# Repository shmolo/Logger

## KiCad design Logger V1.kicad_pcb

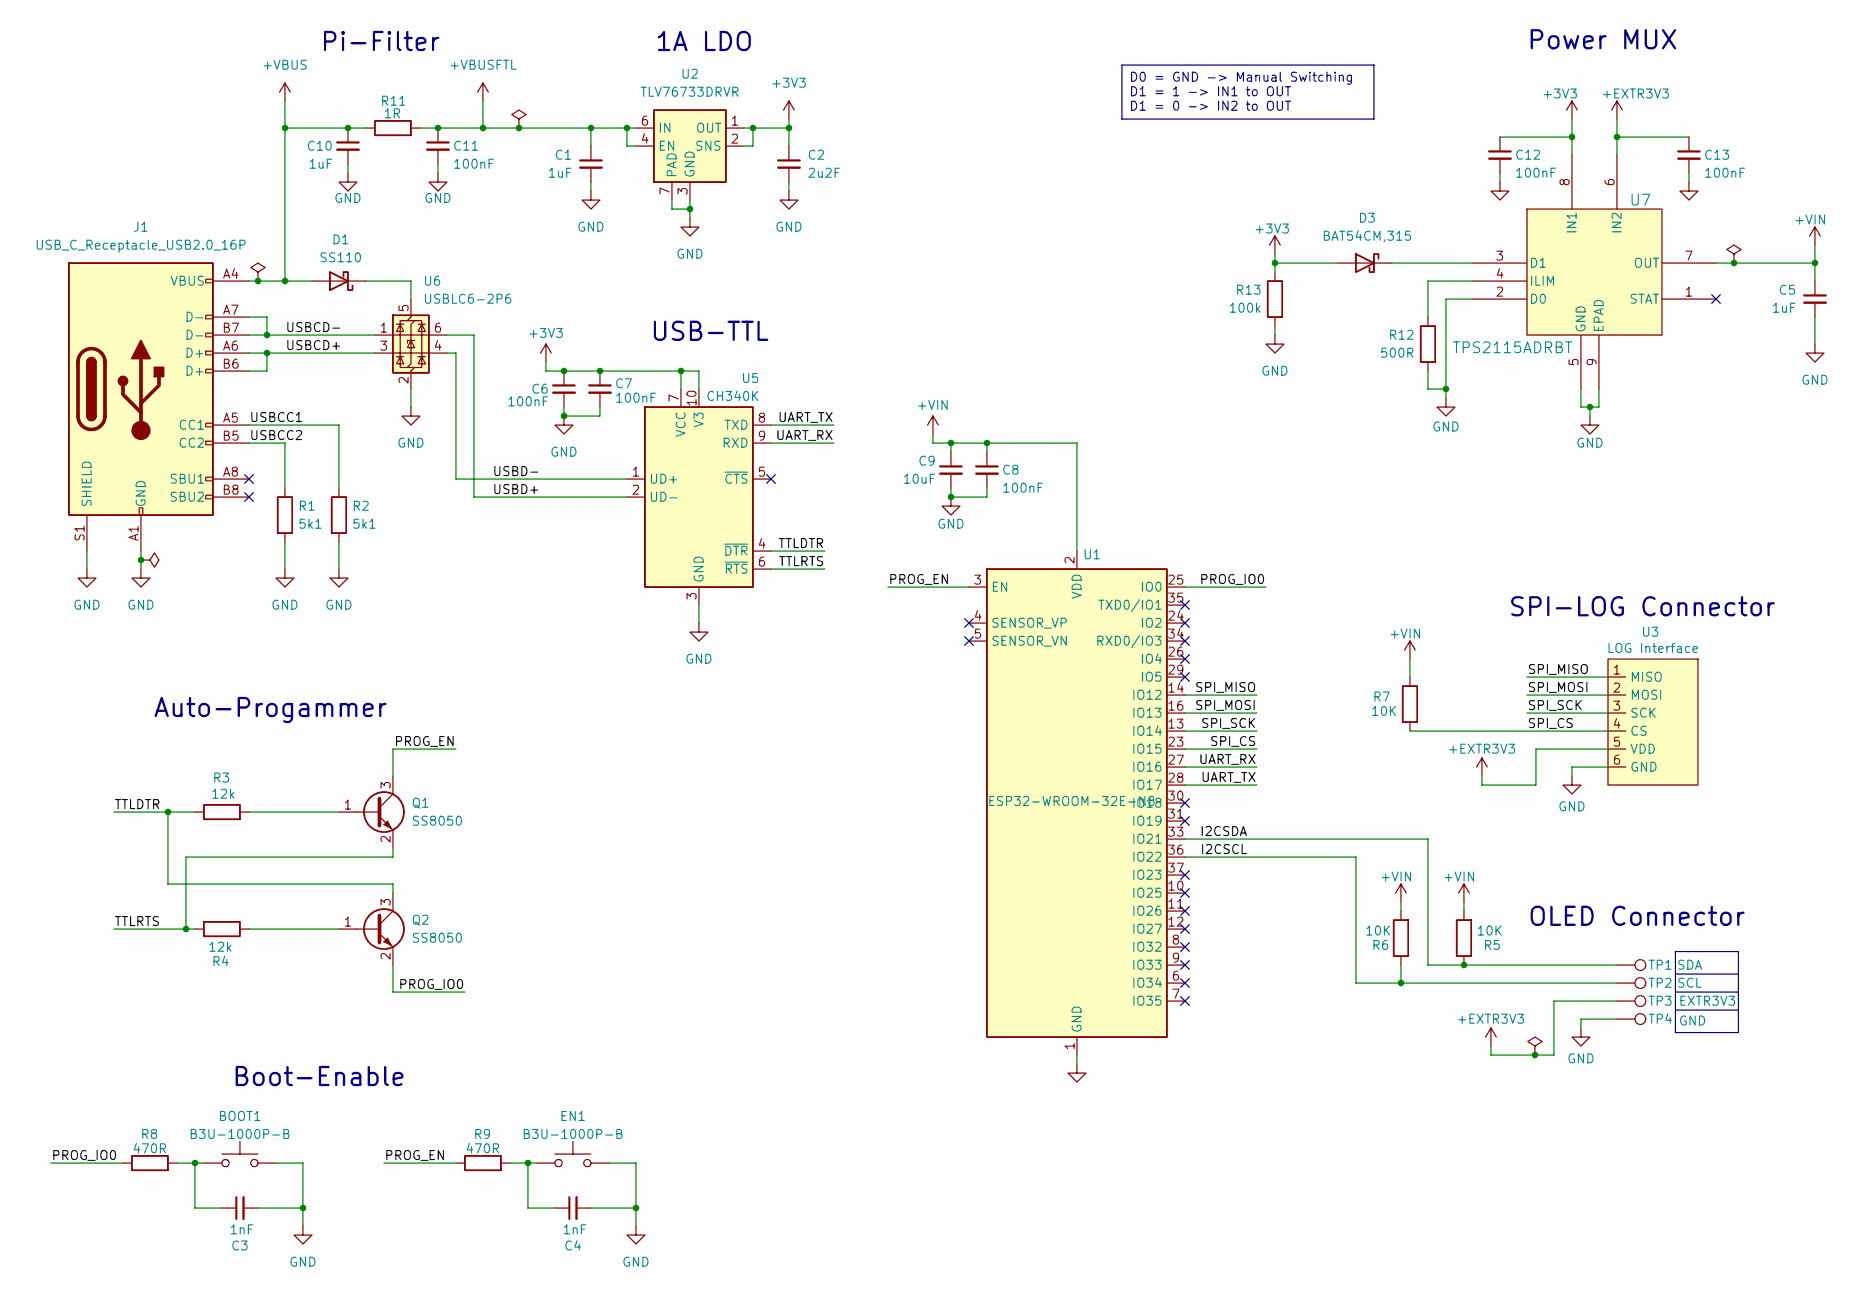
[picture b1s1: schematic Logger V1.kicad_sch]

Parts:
BOOT1: B3U-1000P-B; SW_SPST_B3U-1000P-B; JLC.NUM C231329
C1, C5, C10: 1uF; C_0603_1608Metric_Pad1.08x0.95mm_HandSolder; JLC.NUM C5673
C2: 2u2F; C_0603_1608Metric_Pad1.08x0.95mm_HandSolder; JLC.NUM C23630
C3, C4: 1nF; C_0402_1005Metric_Pad0.74x0.62mm_HandSolder; JLC.NUM C2649506
C6, C7, C8, C11, C12, C13: 100nF; C_0402_1005Metric_Pad0.74x0.62mm_HandSolder; JLC.NUM C100072
C9: 10uF; C_0603_1608Metric_Pad1.08x0.95mm_HandSolder; JLC.NUM C96446
D1: SS110; D_SMA; JLC.NUM C143192
D3: BAT54CM,315; Diodes_DFN1006-3; JLC.NUM C549275
EN1: B3U-1000P-B; SW_SPST_B3U-1000P-B; JLC.NUM C231329
J1: USB_C_Receptacle_USB2.0_16P; USB_C_Receptacle_GCT_USB4105-xx-A_16P_TopMnt_Horizontal; JLC.NUM C3020560
Q1, Q2: SS8050; SOT-23; JLC.NUM C111765
R1, R2: 5k1; R_0402_1005Metric_Pad0.72x0.64mm_HandSolder; JLC.NUM C105872
R3, R4: 12k; R_0402_1005Metric_Pad0.72x0.64mm_HandSolder; JLC.NUM C114760
R5, R6, R7: 10K; R_0402_1005Metric_Pad0.72x0.64mm_HandSolder; JLC.NUM C60489
R8, R9: 470R; R_0402_1005Metric_Pad0.72x0.64mm_HandSolder; JLC.NUM C114949
R11: 1R; R_0603_1608Metric_Pad0.98x0.95mm_HandSolder; JLC.NUM C873679
R12: 500R; R_0402_1005Metric_Pad0.72x0.64mm_HandSolder; JLC.NUM C6460545
R13: 100k; R_0402_1005Metric_Pad0.72x0.64mm_HandSolder; JLC.NUM C60491
TP1: SDA; TestPoint_Pad_1.0x1.0mm
TP2: SCL; TestPoint_Pad_1.0x1.0mm
TP3: EXTR3V3; TestPoint_Pad_1.0x1.0mm
TP4: GND; TestPoint_Pad_1.0x1.0mm
U1: ESP32-WROOM-32E-N8; ESP32-WROOM-32E; JLC.NUM C701342
U2: TLV76733DRVR; WSON-6-1EP_2x2mm_P0.65mm_EP1x1.6mm
U3: LOG Interface; PinHeader_1x06_P2.54mm_Vertical; JLC.NUM C5444523
U5: CH340K; SSOP-10-1EP_3.9x4.9mm_P1mm_EP2.1x3.3mm; JLC.NUM C968586
U6: USBLC6-2P6; SOT-666; JLC.NUM C15999
U7: TPS2115ADRBT; DRB8_2P4X1P65; JLC.NUM C2863458

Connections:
+3V3: C2.1, C6.1, C7.1, C12.1, D3.2 (A), R13.1, U2.1 (OUT), U2.2 (SNS), U5.7 (VCC), U5.10 (V3), U7.8 (IN1)
+EXTR3V3: C13.1, TP3.1, U3.5 (VDD), U7.6 (IN2)
+VBUS: C10.1, D1.2 (A), J1.A4 (VBUS), J1.A9 (VBUS), J1.B4 (VBUS), J1.B9 (VBUS), R11.1
+VBUSFTL: C1.1, C11.1, R11.2, U2.4 (EN), U2.6 (IN)
+VIN: C5.1, C8.1, C9.1, R5.2, R6.2, R7.1, U1.2 (VDD), U7.7 (OUT)
/I2CSCL: R6.1, TP2.1, U1.36 (IO22)
/I2CSDA: R5.1, TP1.1, U1.33 (IO21)
/PROG_EN: Q1.3 (C), R9.1, U1.3 (EN)
/PROG_IO0: Q2.2 (E), R8.1, U1.25 (IO0)
/SPI_CS: R7.2, U1.23 (IO15), U3.4 (CS)
/SPI_MISO: U1.14 (IO12), U3.1 (MISO)
/SPI_MOSI: U1.16 (IO13), U3.2 (MOSI)
/SPI_SCK: U1.13 (IO14), U3.3 (SCK)
/TTLDTR: Q2.3 (C), R3.1, U5.4 (~DTR)
/TTLRTS: Q1.2 (E), R4.2, U5.6 (~RTS)
/UART_RX: U1.27 (IO16), U5.9 (RXD)
/UART_TX: U1.28 (IO17), U5.8 (TXD)
/USBCC1: J1.A5 (CC1), R2.1
/USBCC2: J1.B5 (CC2), R1.1
/USBCD+: J1.A6 (D+), J1.B6 (D+), U6.3 (I/O2)
/USBCD-: J1.A7 (D-), J1.B7 (D-), U6.1 (I/O1)
/USBD+: U5.2 (UD-), U6.6 (I/O1)
/USBD-: U5.1 (UD+), U6.4 (I/O2)
GND: BOOT1.2, C1.2, C2.2, C3.2, C4.2, C5.2, C6.2, C7.2, C8.2, C9.2, C10.2, C11.2, C12.2, C13.2, EN1.2, J1.A1 (GND), J1.A12 (GND), J1.B1 (GND), J1.B12 (GND), J1.S1 (SHIELD), R1.2, R2.2, R12.2, R13.2, TP4.1, U1.1 (GND), U1.15 (GND), U1.38 (GND), U1.39 (GND), U2.3 (GND), U2.5 (GND), U2.7 (PAD), U3.6 (GND), U5.3 (GND), U5.11 (GND), U6.2 (GND), U7.2 (D0), U7.5 (GND), U7.9 (EPAD)
unnamed: BOOT1.1, C3.1, R8.2
unnamed: C4.1, EN1.1, R9.2
unnamed: D1.1 (K), U6.5 (VBUS)
unnamed: D3.1 (K), U7.3 (D1)
unnamed: Q1.1 (B), R3.2
unnamed: Q2.1 (B), R4.1
unnamed: R12.1, U7.4 (ILIM)

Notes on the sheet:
SPI-LOG Connector
Auto-Progammer
OLED Connector
USB-TTL
Boot-Enable
1A LDO
Pi-Filter
Power MUX
D0 = GND -> Manual Switching D1 = 1 -> IN1 to OUT D1 = 0 -> IN2 to OUT

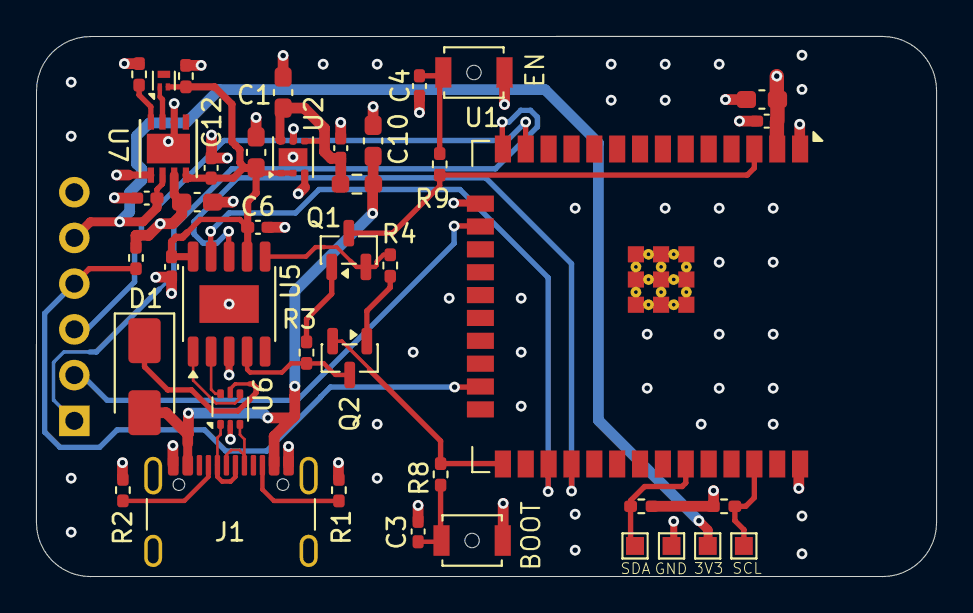
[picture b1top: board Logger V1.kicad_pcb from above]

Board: 4 copper layers, 50.0 x 30.0 mm, 42 parts (1 on the bottom side), 31 nets.

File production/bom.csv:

Designator,Footprint,Quantity,Value,LCSC Part #
"BOOT, EN",SW_SPST_B3U-1000P-B,2,B3U-1000P-B,
"C1, C10, C12",0603,3,1uF,
"C11, C13, C14, C6, C7, C8",0402,6,100nF,
C2,0603,1,2u2F,
"C3, C4",0402,2,1nF,
C9,0603,1,10uF,
D1,D_SMA,1,SS110,
D3,Diodes_DFN1006-3,1,"BAT54CM,315",
J1,USB_C_Receptacle_GCT_USB4105-xx-A_16P_TopMnt_Horizontal,1,USB_C_Receptacle_USB2.0_16P,
"Q1, Q2",SOT-23,2,SS8050,
"R1, R2",0402,2,5k1,
R11,0603,1,1R,
R12,0402,1,500R,
R13,0402,1,100k,
"R3, R4",0402,2,12k,
"R5, R6, R7",0402,3,10K,
"R8, R9",0402,2,470R,
"TP1, TP2, TP3, TP4",TestPoint_Pad_1.0x1.0mm,4,TestPoint,
U1,ESP32-WROOM-32E,1,ESP32-WROOM-32E-N8,
U2,WSON-6-1EP_2x2mm_P0.65mm_EP1x1.6mm,1,TLV76733DRVR,
U3,PinHeader_1x06_P2.54mm_Vertical,1,LOG Interface,
U5,SSOP-10-1EP_3.9x4.9mm_P1mm_EP2.1x3.3mm,1,CH340K,
U6,SOT-666,1,USBLC6-2P6,
U7,DRB8_2P4X1P65,1,TPS2115ADRBT,

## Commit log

2025-12-03 Everything initialized, Power MUX is left in schematic
2025-12-04 Schematic Finalized
2025-12-05 PCB Rev 1.0
2025-12-06 ATIC Logger Rev1.0
2025-12-06 Logger Board Rev1.0
